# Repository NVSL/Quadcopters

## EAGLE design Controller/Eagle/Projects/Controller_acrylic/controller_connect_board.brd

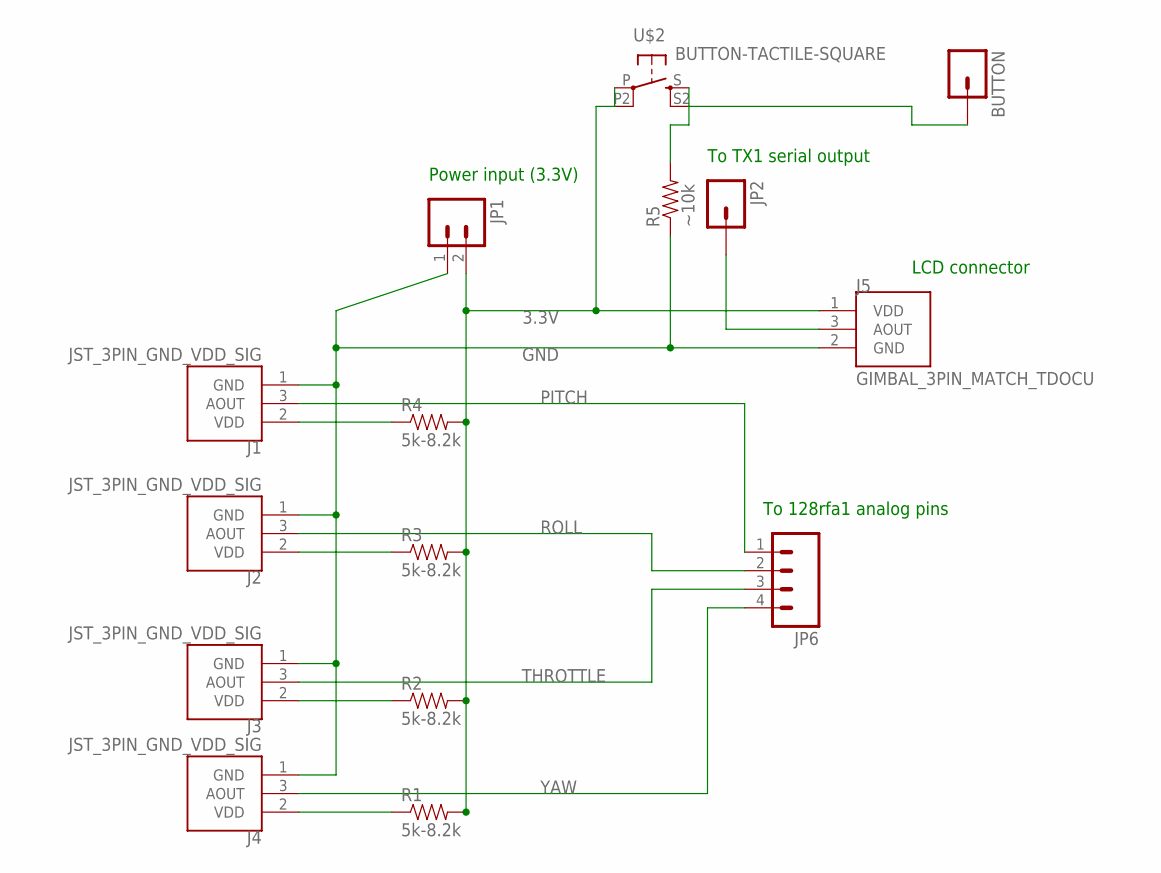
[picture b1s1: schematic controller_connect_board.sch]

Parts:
BUTTON: M01PTH; 1X01
J1, J2, J3, J4: JST_3PIN_GND_VDD_SIG; JST-3-PTH-REVERSE
J5: GIMBAL_3PIN_MATCH_TDOCU; JST-3-PTH
JP1: M021X02_NO_SILK; 1X02_NO_SILK
JP2: M01PTH; 1X01
JP6: M04PTH; 1X04
R1, R2, R3, R4: 5k-8.2k; AXIAL-0.4
R5: ~10k; AXIAL-0.4
U$2: BUTTON-TACTILE-SQUARE; BUTTON-TACTILE-SQUARE-ADAFRUIT1010

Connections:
3.3V: J5.1 (VDD), JP1.2, R1.P$2 (2), R2.P$2 (2), R3.P$2 (2), R4.P$2 (2), U$2.P, U$2.P2 (P1)
GND: J1.1 (GND), J2.1 (GND), J3.1 (GND), J4.1 (GND), J5.2 (GND), JP1.1, R5.P$1 (1)
unnamed: J4.2 (VDD), R1.P$1 (1)
unnamed: J3.2 (VDD), R2.P$1 (1)
unnamed: J2.2 (VDD), R3.P$1 (1)
unnamed: J1.2 (VDD), R4.P$1 (1)
unnamed: BUTTON.1, R5.P$2 (2), U$2.S, U$2.S2 (S1)
unnamed: J5.3 (AOUT), JP2.1
PITCH: J1.3 (AOUT), JP6.1
ROLL: J2.3 (AOUT), JP6.2
THROTTLE: J3.3 (AOUT), JP6.3
YAW: J4.3 (AOUT), JP6.4

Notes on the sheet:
Power input (3.3V)
To 128rfa1 analog pins
LCD connector
To TX1 serial output

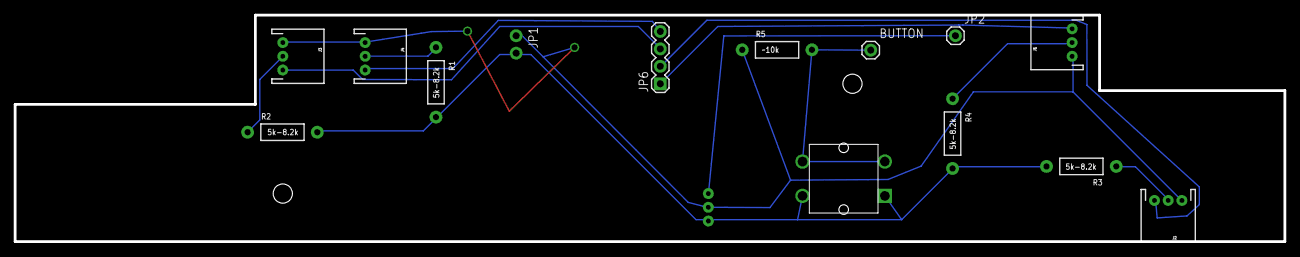
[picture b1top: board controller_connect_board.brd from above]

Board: 2 copper layers, 185.0 x 33.0 mm, 16 parts (1 on the bottom side), 12 nets.

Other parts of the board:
U$1: CONNECTOR_BOARD_OUTLINE

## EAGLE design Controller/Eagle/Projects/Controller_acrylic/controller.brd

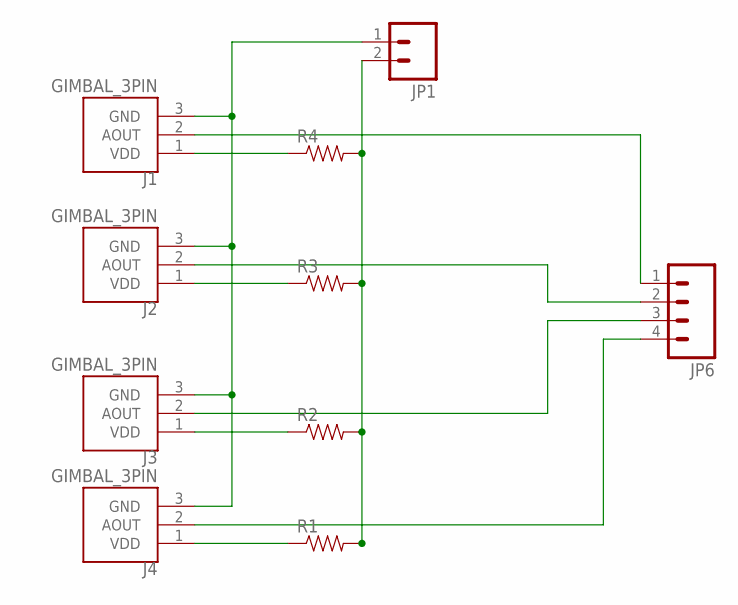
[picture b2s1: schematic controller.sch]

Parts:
J1, J2, J3, J4: GIMBAL_3PIN; JST-3-PTH
JP1: M02LOCK; 1X02_LOCK
JP6: M04PTH; 1X04
R1, R2, R3, R4: RESISTORPTH-1/6W; 1/6W-RES

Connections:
3.3V: JP1.2, R1.2, R2.2, R3.2, R4.2
GND: J1.3 (GND), J2.3 (GND), J3.3 (GND), J4.3 (GND), JP1.1
unnamed: J4.1 (VDD), R1.1
unnamed: J3.1 (VDD), R2.1
unnamed: J2.1 (VDD), R3.1
unnamed: J1.1 (VDD), R4.1
unnamed: J1.2 (AOUT), JP6.1
unnamed: J2.2 (AOUT), JP6.2
unnamed: J3.2 (AOUT), JP6.3
unnamed: J4.2 (AOUT), JP6.4

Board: 2 copper layers, 15 parts (1 on the bottom side), 10 nets, no tracks yet.

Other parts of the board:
U$1, U$2: GIMBAL_FOOTPRINT
U$3: ATMEGA128RFA1
U$4: SPARKFUN_LCD_33
U$5: CONTROLLER_OUTLINE

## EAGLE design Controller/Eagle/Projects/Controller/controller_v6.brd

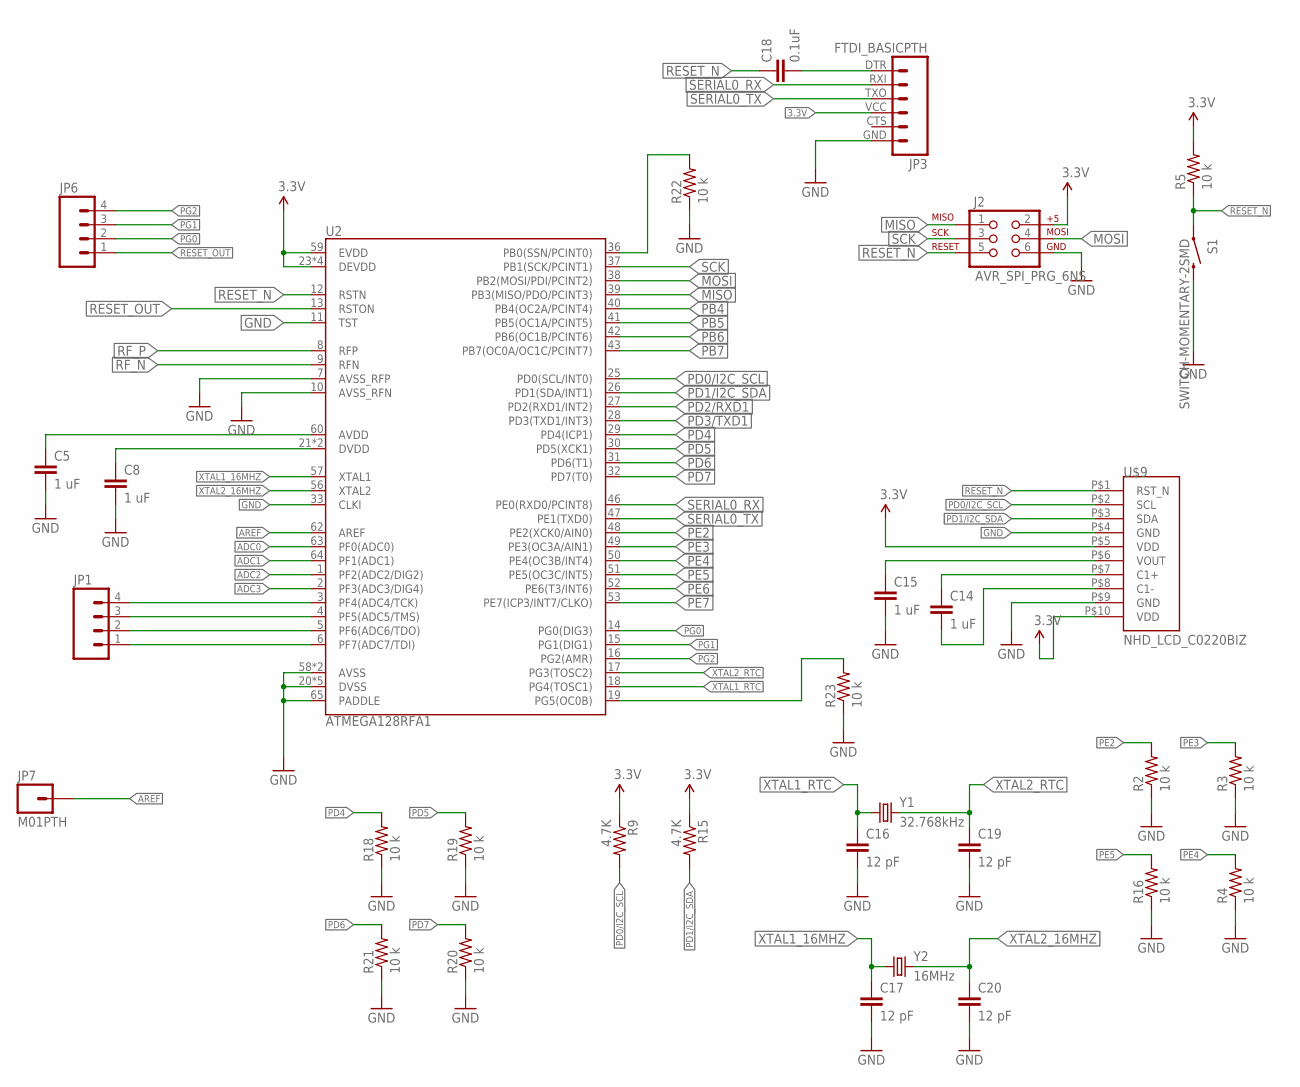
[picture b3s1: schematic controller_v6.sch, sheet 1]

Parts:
C5, C8, C14, C15: 1 uF; 0805
C16, C17, C19, C20: 12 pF; 0805
C18: 0.1uF; 0805
J2: AVR_SPI_PRG_6NS; 2X3-NS
JP1, JP6: M04PTH; 1X04
JP3: FTDI_BASICPTH; FTDI_BASIC
JP7: M01PTH; 1X01
R2, R3, R4, R5, R16, R18, R19, R20, R21, R22, R23: 10 k; 0805
R9, R15: 4.7K; 0805
S1: SWITCH-MOMENTARY-2SMD; TACTILE_SWITCH_SMD
U2: ATMEGA128RFA1; QFN-64
U$9: NHD_LCD_C0220BIZ; 1X08-2MMPTH-LCD
Y1: 32.768kHz; CRYSTAL-32KHZ-SMD
Y2: 16MHz; CRYSTAL-SMD-5X3

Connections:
3.3V: J2.2, JP3.VCC (4), R5.2, R9.1, R15.1, U2.23 (DEVDD), U2.34 (DEVDD), U2.44 (DEVDD), U2.54 (DEVDD), U2.59 (EVDD), U$9.P$5 (VDD), U$9.P$10 (VDD); also elsewhere on the board
ADC0: U2.63 (PF0(ADC0)); also elsewhere on the board
ADC1: U2.64 (PF1(ADC1)); also elsewhere on the board
ADC2: U2.1 (PF2(ADC2/DIG2)); also elsewhere on the board
ADC3: U2.2 (PF3(ADC3/DIG4)); also elsewhere on the board
ADC4: JP1.4, U2.3 (PF4(ADC4/TCK))
ADC5: JP1.3, U2.4 (PF5(ADC5/TMS))
ADC6: JP1.2, U2.5 (PF6(ADC6/TDO))
ADC7: JP1.1, U2.6 (PF7(ADC7/TDI))
AREF: JP7.1, U2.62 (AREF)
GND: C5.2, C8.2, C15.2, C16.2, C17.2, C19.2, C20.2, J2.6, JP3.GND (6), R2.1, R3.1, R4.1, R16.1, R18.1, R19.1, R20.1, R21.1, R22.1, R23.1, S1.3 (2), U2.7 (AVSS_RFP), U2.10 (AVSS_RFN), U2.11 (TST), U2.20 (DVSS), U2.24 (DVSS), U2.33 (CLKI), U2.35 (DVSS), U2.45 (DVSS), U2.55 (DVSS), U2.58 (AVSS), U2.61 (AVSS), U2.65 (PADDLE), U$9.P$4 (GND), U$9.P$9 (GND); also elsewhere on the board
MISO: J2.1, U2.39 (PB3(MISO/PDO/PCINT3))
MOSI: J2.4, U2.38 (PB2(MOSI/PDI/PCINT2))
unnamed: C18.2, JP3.DTR (1)
unnamed: C14.1, U$9.P$7 (C1+)
unnamed: C5.1, U2.60 (AVDD)
unnamed: C8.1, U2.21 (DVDD), U2.22 (DVDD)
unnamed: C14.2, U$9.P$8 (C1-)
PB0: R22.2, U2.36 (PB0(SSN/PCINT0))
PB1: R23.2, U2.19 (PG5(OC0B))
PB4: U2.40 (PB4(OC2A/PCINT4)); also elsewhere on the board
PB5: U2.41 (PB5(OC1A/PCINT5)); also elsewhere on the board
PB6: U2.42 (PB6(OC1B/PCINT6)); also elsewhere on the board
PB7: U2.43 (PB7(OC0A/OC1C/PCINT7)); also elsewhere on the board
PD0/I2C_SCL: R9.2, U2.25 (PD0(SCL/INT0)), U$9.P$2 (SCL)
PD1/I2C_SDA: R15.2, U2.26 (PD1(SDA/INT1)), U$9.P$3 (SDA)
PD2/RXD1: U2.27 (PD2(RXD1/INT2)); also elsewhere on the board
PD3/TXD1: U2.28 (PD3(TXD1/INT3)); also elsewhere on the board
PD4: R18.2, U2.29 (PD4(ICP1))
PD5: R19.2, U2.30 (PD5(XCK1))
PD6: R21.2, U2.31 (PD6(T1))
PD7: R20.2, U2.32 (PD7(T0))
PE2: R2.2, U2.48 (PE2(XCK0/AIN0))
PE3: R3.2, U2.49 (PE3(OC3A/AIN1))
PE4: R4.2, U2.50 (PE4(OC3B/INT4))
PE5: R16.2, U2.51 (PE5(OC3C/INT5))
PE6: U2.52 (PE6(T3/INT6)); also elsewhere on the board
PE7: U2.53 (PE7(ICP3/INT7/CLKO)); also elsewhere on the board
PG0: JP6.2, U2.14 (PG0(DIG3))
PG1: JP6.3, U2.15 (PG1(DIG1))
PG2: JP6.4, U2.16 (PG2(AMR))
RESET_N: C18.1, J2.5, R5.1, S1.1, U2.12 (RSTN), U$9.P$1 (RST_N)
RESET_OUT: JP6.1, U2.13 (RSTON)
RF_N: U2.9 (RFN); also elsewhere on the board
RF_P: U2.8 (RFP); also elsewhere on the board
SCK: J2.3, U2.37 (PB1(SCK/PCINT1))
SERIAL0_RX: JP3.RXI (2), U2.46 (PE0(RXD0/PCINT8))
SERIAL0_TX: JP3.TXO (3), U2.47 (PE1(TXD0))
VOUT: C15.1, U$9.P$6 (VOUT)
XTAL1_16MHZ: C17.1, U2.57 (XTAL1), Y2.1
XTAL1_RTC: C16.1, U2.18 (PG4(TOSC1)), Y1.X1 (1)
XTAL2_16MHZ: C20.1, U2.56 (XTAL2), Y2.3 (2)
XTAL2_RTC: C19.1, U2.17 (PG3(TOSC2)), Y1.X2 (2)

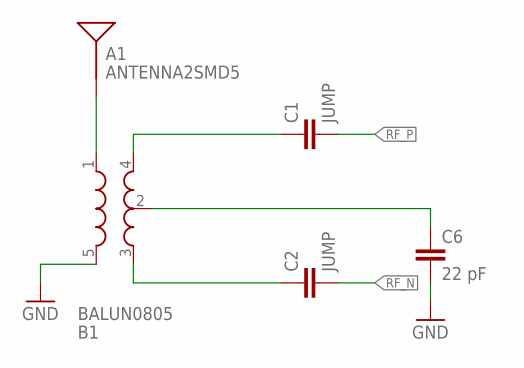
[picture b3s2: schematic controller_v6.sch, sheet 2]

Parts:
A1: ANTENNA2SMD5; ANTENNA-CHIP5
B1: BALUN0805; BALUN
C1, C2: JUMP; 0805
C6: 22 pF; 0805

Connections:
GND: B1.5 (GND), C6.2; also elsewhere on the board
unnamed: B1.4 (OUT1), C1.1
unnamed: B1.3 (OUT2), C2.1
unnamed: B1.2 (GND), C6.1
unnamed: A1.FEED, B1.1 (IN)
RF_N: C2.2; also elsewhere on the board
RF_P: C1.2; also elsewhere on the board

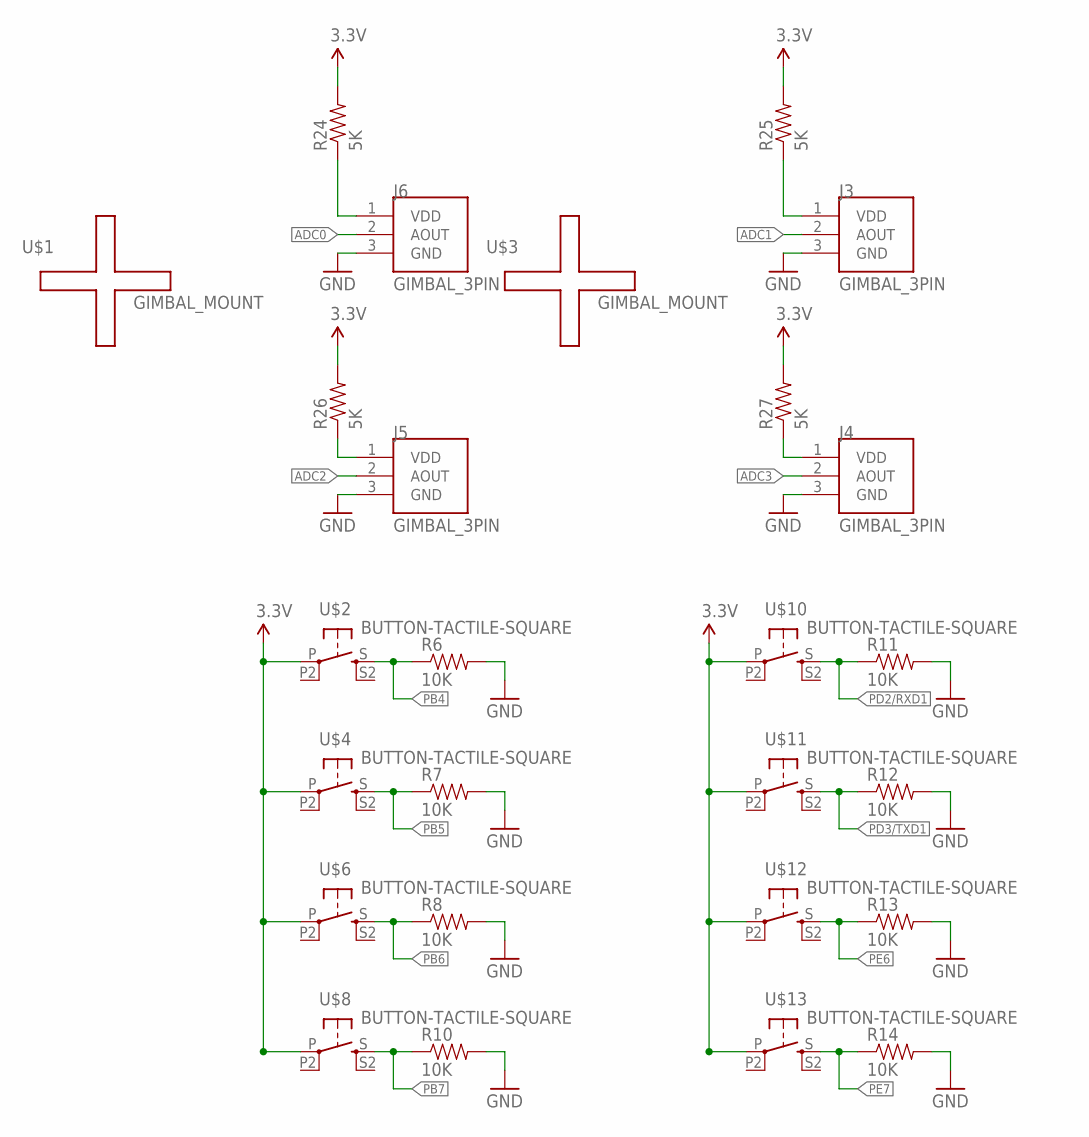
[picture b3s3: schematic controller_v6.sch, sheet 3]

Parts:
J3, J4, J5, J6: GIMBAL_3PIN; JST-3-PTH
R6, R7, R8, R10, R11, R12, R13, R14: 10K; 0805
R24, R25, R26, R27: 5K; 0805
U$1, U$3: GIMBAL_MOUNT; GIMBAL_FOOTPRINT
U$2, U$4, U$6, U$8, U$10, U$11, U$12, U$13: BUTTON-TACTILE-SQUARE; BUTTON-TACTILE-SQUARE-ADAFRUIT1010

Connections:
3.3V: R24.2, R25.2, R26.2, R27.2, U$2.P, U$4.P, U$6.P, U$8.P, U$10.P, U$11.P, U$12.P, U$13.P; also elsewhere on the board
ADC0: J6.2 (AOUT); also elsewhere on the board
ADC1: J3.2 (AOUT); also elsewhere on the board
ADC2: J5.2 (AOUT); also elsewhere on the board
ADC3: J4.2 (AOUT); also elsewhere on the board
GND: J3.3 (GND), J4.3 (GND), J5.3 (GND), J6.3 (GND), R6.2, R7.2, R8.2, R10.2, R11.2, R12.2, R13.2, R14.2; also elsewhere on the board
unnamed: J6.1 (VDD), R24.1
unnamed: J3.1 (VDD), R25.1
unnamed: J5.1 (VDD), R26.1
unnamed: J4.1 (VDD), R27.1
PB4: R6.1, U$2.S; also elsewhere on the board
PB5: R7.1, U$4.S; also elsewhere on the board
PB6: R8.1, U$6.S; also elsewhere on the board
PB7: R10.1, U$8.S; also elsewhere on the board
PD2/RXD1: R11.1, U$10.S; also elsewhere on the board
PD3/TXD1: R12.1, U$11.S; also elsewhere on the board
PE6: R13.1, U$12.S; also elsewhere on the board
PE7: R14.1, U$13.S; also elsewhere on the board

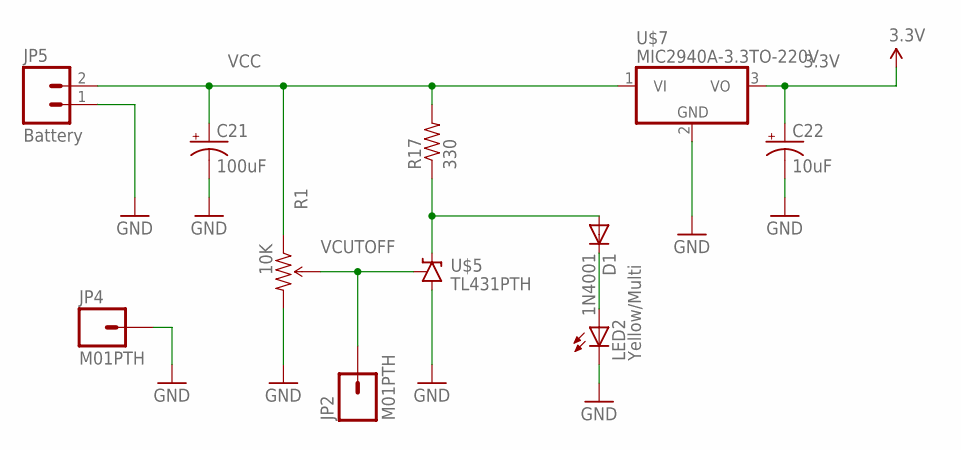
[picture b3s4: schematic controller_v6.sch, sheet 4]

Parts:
C21: 100uF; E3,5-8
C22: 10uF; E2,5-5
D1: 1N4001; DO41-10
JP2, JP4: M01PTH; 1X01
JP5: Battery; 1X02
LED2: Yellow/Multi; LED5MM
R1: 10K; 3386U
R17: 330; AXIAL-0.3
U$5: TL431PTH; TO-92
U$7: MIC2940A-3.3TO-220V; TO-220V

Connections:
3.3V: C22.+, U$7.3 (VO); also elsewhere on the board
GND: C21.-, C22.-, JP4.1, JP5.1, LED2.K (C), R1.3 (CW), U$5.2 (A), U$7.2 (GND); also elsewhere on the board
unnamed: D1.A, R17.P$1 (1), U$5.3 (C)
unnamed: D1.C, LED2.A
VCC: C21.+, JP5.2, R1.1 (CCW), R17.P$2 (2), U$7.1 (VI)
VCUTOFF: JP2.1, R1.2 (WIPER), U$5.1 (R)

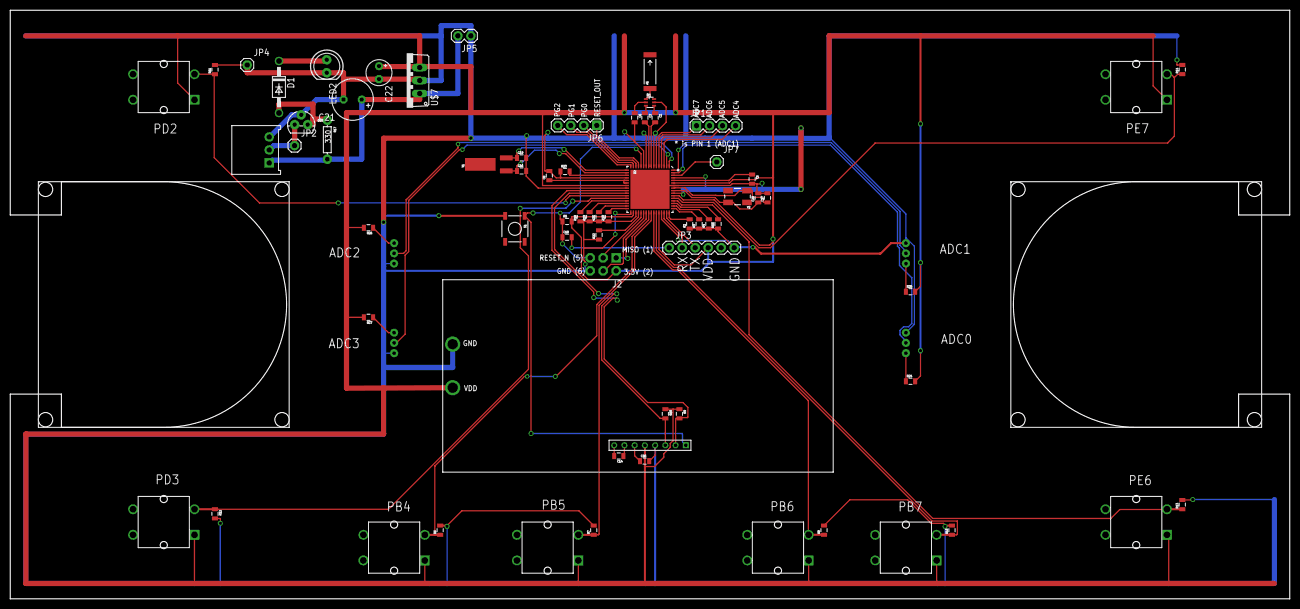
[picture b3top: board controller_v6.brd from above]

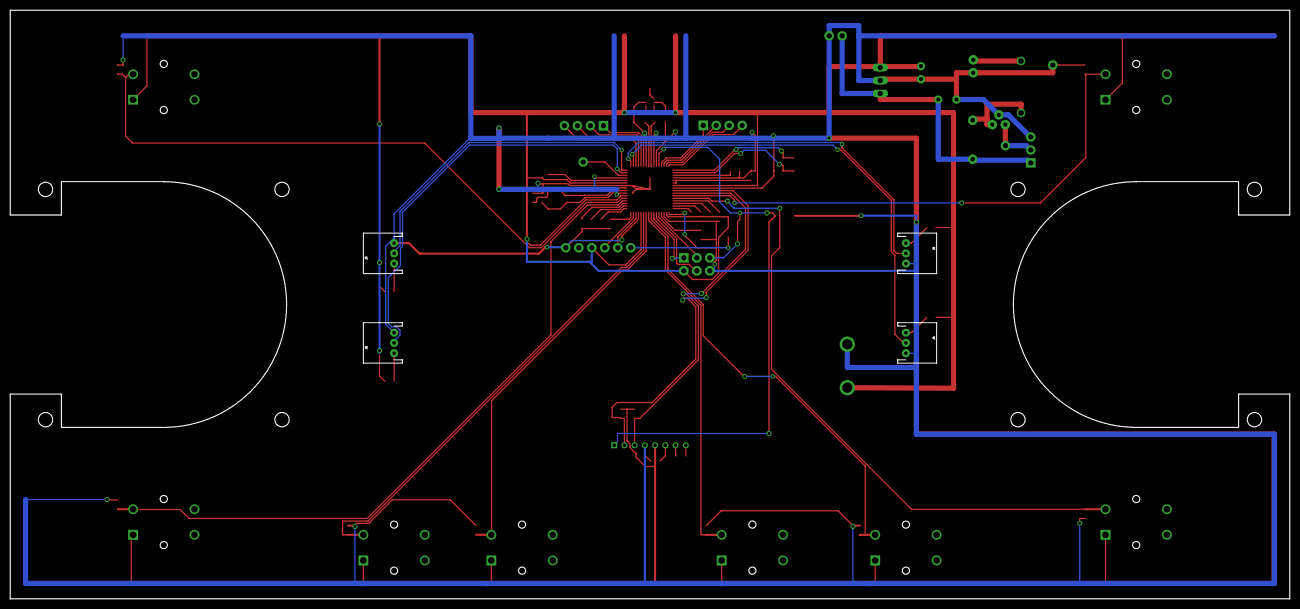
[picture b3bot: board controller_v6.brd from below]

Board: 2 copper layers, 250.0 x 115.0 mm, 74 parts (4 on the bottom side), 65 nets.

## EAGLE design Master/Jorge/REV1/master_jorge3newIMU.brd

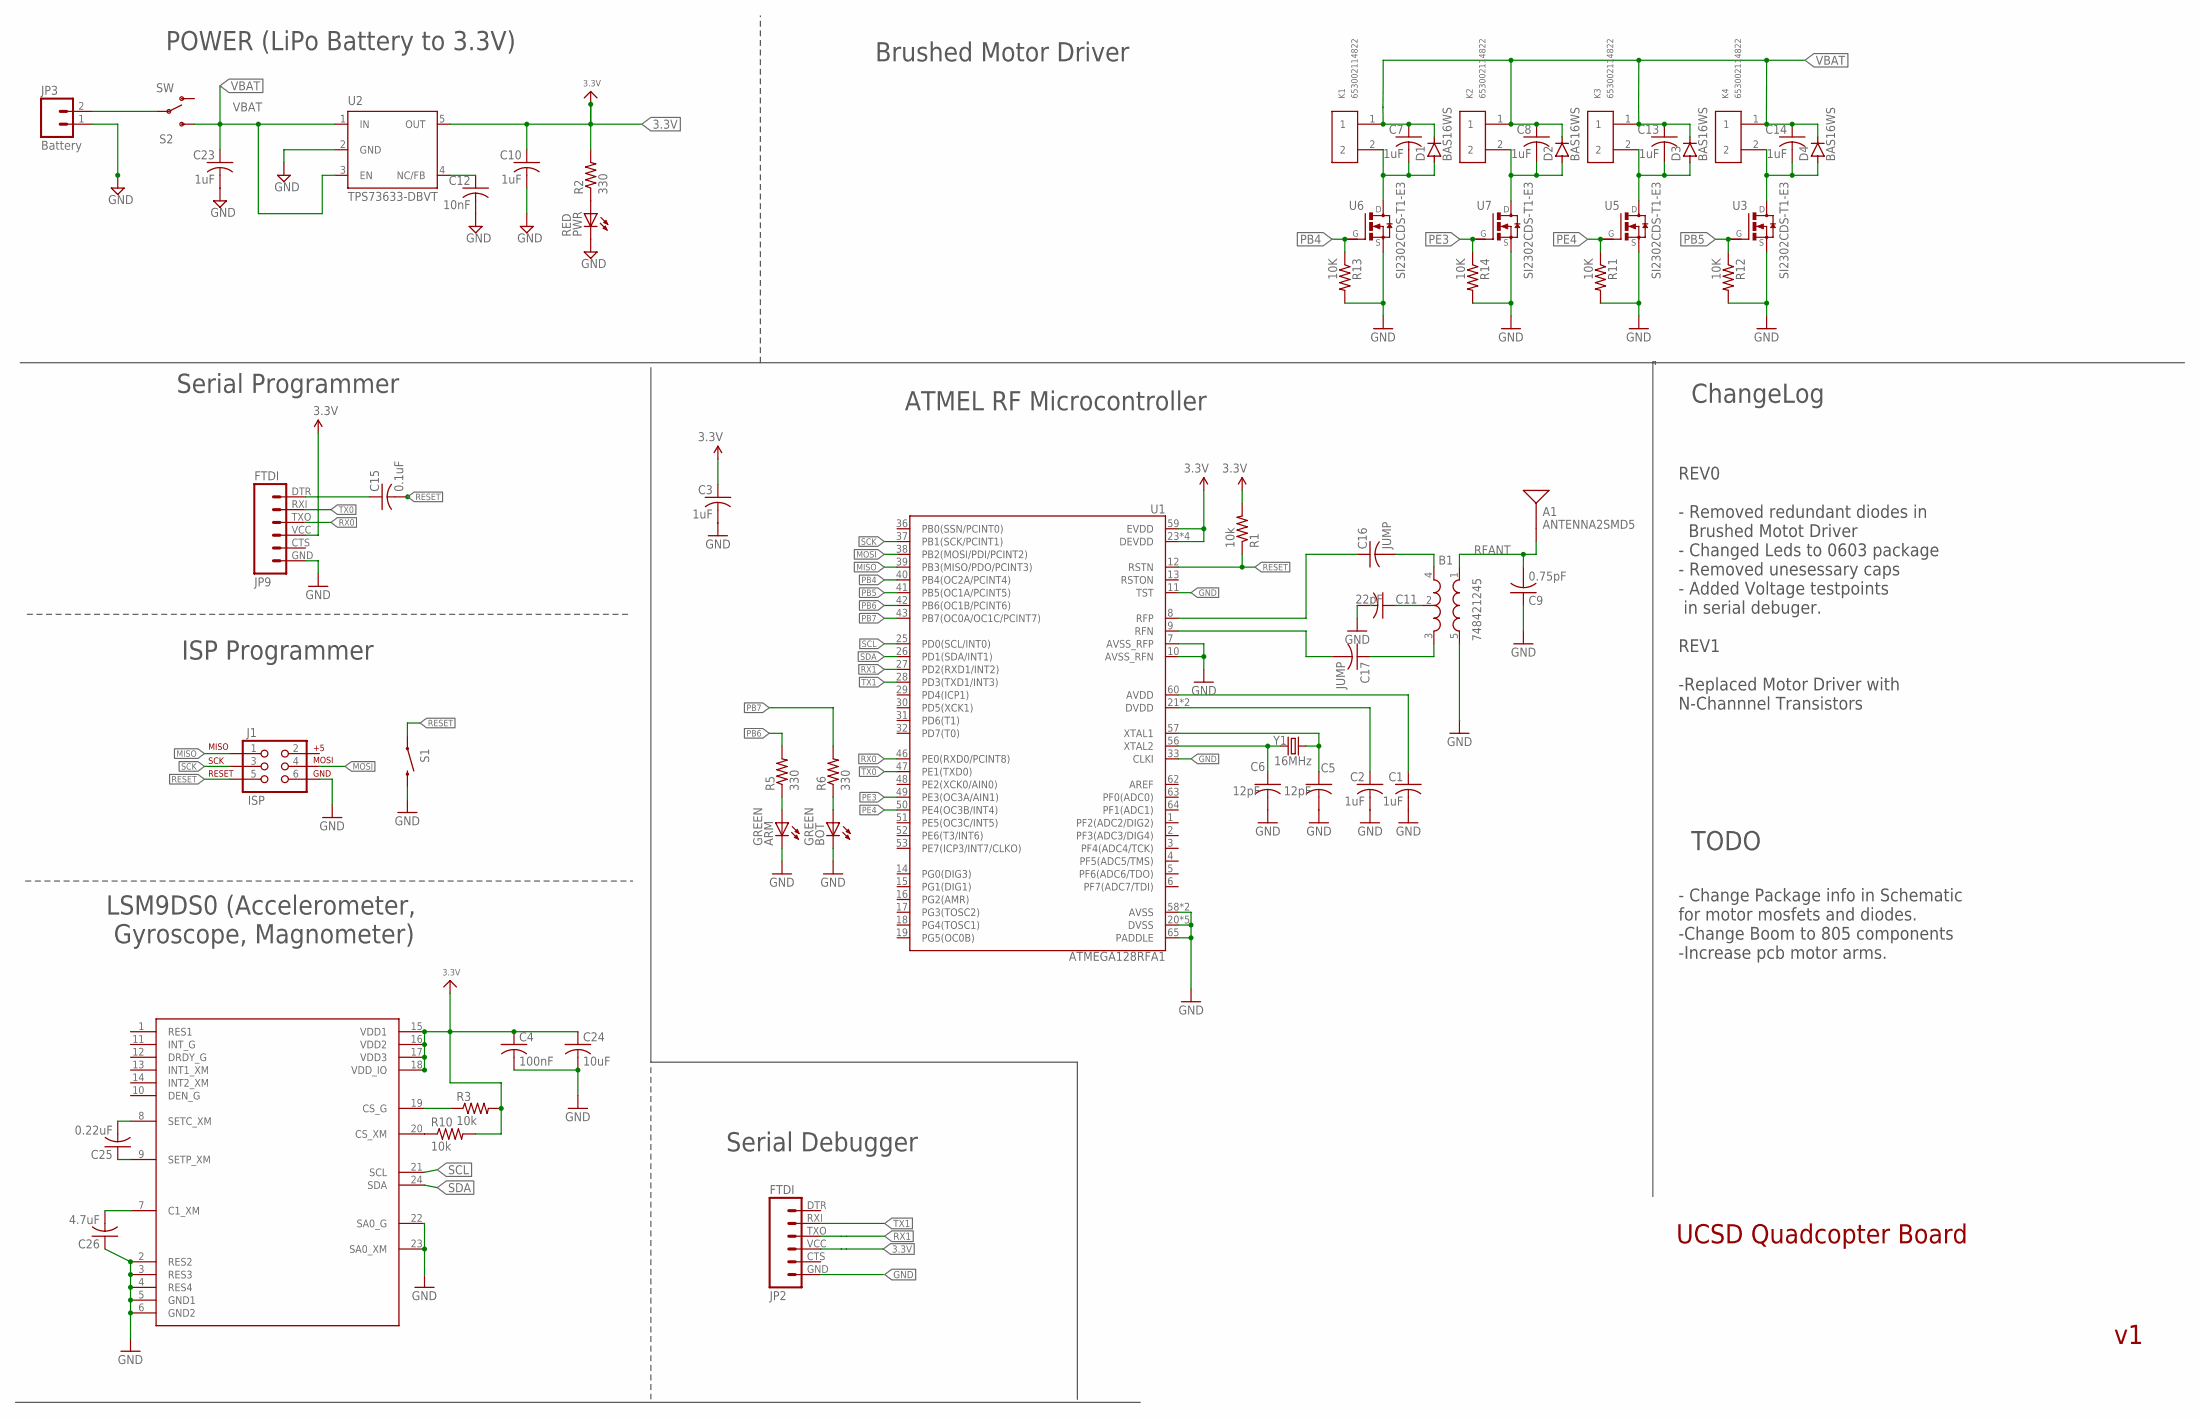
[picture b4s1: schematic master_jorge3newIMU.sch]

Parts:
A1: ANTENNA2SMD5; ANTENNA-CHIP5
ARM: GREEN; CHIP-LED0805
B1: 748421245; BALUN
BOT: GREEN; CHIP-LED0805
C1, C2, C3, C7, C8, C10, C13, C14, C23: 1uF; C0805
C4: 100nF; C0805
C5, C6: 12pF; C0805
C9: 0.75pF; C0805
C11: 22pF; C0805
C12: 10nF; C0805
C15: 0.1uF; C0805
C16, C17: JUMP; C0805
C24: 10uF; C0805
C25: 0.22uF; C0805
C26: 4.7uF; C0805
D1, D2, D3, D4: BAS16WS; SOD323_ST
J1: ISP; 2X3-NS
JP2, JP9: FTDI; FTDI_BASIC
JP3: Battery; 1X02
K1, K2, K3, K4: 653002114822
PWR: RED; CHIP-LED0805
R1, R3, R10: 10k; R0805
R2, R5, R6: 330; R0805
R11, R12, R13, R14: 10K; R0805
S1: SWITCH-MOMENTARY-2SMD; TACTILE_SWITCH_SMD
S2: SW; SWITCH-SPDT
U1: ATMEGA128RFA1; QFN-64
U2: TPS73633-DBVT; SOT23-DBV
U3, U5, U6, U7: SI2302CDS-T1-E3; SOT95P237X112-3N
U4: LSM9DS0; LGA-24
Y1: 16MHz; CRYSTAL-SMD-5X3

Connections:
3.3V: C3.1, C4.1, C10.1, C24.1, JP2.VCC (4), JP9.VCC (4), R1.2, R2.2, R3.2, R10.2, U1.23 (DEVDD), U1.34 (DEVDD), U1.44 (DEVDD), U1.54 (DEVDD), U1.59 (EVDD), U2.5 (OUT), U4.15 (VDD1), U4.16 (VDD2), U4.17 (VDD3), U4.18 (VDD_IO)
AVDD: C1.1, U1.60 (AVDD)
DTR: C15.1, JP9.DTR (1)
DVDD: C2.1, U1.21 (DVDD), U1.22 (DVDD)
GND: ARM.C, B1.5 (GND), BOT.C, C1.2, C2.2, C3.2, C4.2, C5.2, C6.2, C9.1, C10.2, C11.2, C12.2, C23.2, C24.2, C26.1, J1.6, JP2.GND (6), JP3.1, JP9.GND (6), PWR.C, R11.2, R12.2, R13.2, R14.2, S1.3 (2), U1.7 (AVSS_RFP), U1.10 (AVSS_RFN), U1.11 (TST), U1.20 (DVSS), U1.24 (DVSS), U1.33 (CLKI), U1.35 (DVSS), U1.45 (DVSS), U1.55 (DVSS), U1.58 (AVSS), U1.61 (AVSS), U1.65 (PADDLE), U2.2 (GND), U3.2 (S), U4.2 (RES2), U4.3 (RES3), U4.4 (RES4), U4.5 (GND1), U4.6 (GND2), U4.22 (SA0_G), U4.23 (SA0_XM), U5.2 (S), U6.2 (S), U7.2 (S)
MISO: J1.1, U1.39 (PB3(MISO/PDO/PCINT3))
MOSI: J1.4, U1.38 (PB2(MOSI/PDI/PCINT2))
unnamed: C12.1, U2.4 (NC/FB)
unnamed: PWR.A, R2.1
unnamed: C5.1, U1.57 (XTAL1), Y1.3 (2)
unnamed: C6.1, U1.56 (XTAL2), Y1.1
unnamed: B1.2 (GND), C11.1
unnamed: ARM.A, R5.1
unnamed: B1.4 (OUT1), C16.2
unnamed: B1.3 (OUT2), C17.1
unnamed: BOT.A, R6.1
unnamed: JP3.2, S2.2
unnamed: C26.2, U4.7 (C1_XM)
unnamed: C25.2, U4.8 (SETC_XM)
unnamed: C25.1, U4.9 (SETP_XM)
unnamed: R3.1, U4.19 (CS_G)
unnamed: R10.1, U4.20 (CS_XM)
unnamed: C7.2, D1.A, K1.2, U6.3 (D)
unnamed: C8.2, D2.A, K2.2, U7.3 (D)
unnamed: C13.2, D3.A, K3.2, U5.3 (D)
unnamed: C14.2, D4.A, K4.2, U3.3 (D)
PB4: R13.1, U1.40 (PB4(OC2A/PCINT4)), U6.1 (G)
PB5: R12.1, U1.41 (PB5(OC1A/PCINT5)), U3.1 (G)
PB6: R5.2, U1.42 (PB6(OC1B/PCINT6))
PB7: R6.2, U1.43 (PB7(OC0A/OC1C/PCINT7))
PE3: R14.1, U1.49 (PE3(OC3A/AIN1)), U7.1 (G)
PE4: R11.1, U1.50 (PE4(OC3B/INT4)), U5.1 (G)
RESET: C15.2, J1.5, R1.1, S1.1, U1.12 (RSTN)
RFANT: A1.FEED, B1.1 (IN), C9.2
RFN: C17.2, U1.9 (RFN)
RFP: C16.1, U1.8 (RFP)
RX0: JP9.TXO (3), U1.46 (PE0(RXD0/PCINT8))
RX1: JP2.TXO (3), U1.27 (PD2(RXD1/INT2))
SCK: J1.3, U1.37 (PB1(SCK/PCINT1))
SCL: U1.25 (PD0(SCL/INT0)), U4.21 (SCL)
SDA: U1.26 (PD1(SDA/INT1)), U4.24 (SDA)
TX0: JP9.RXI (2), U1.47 (PE1(TXD0))
TX1: JP2.RXI (2), U1.28 (PD3(TXD1/INT3))
VBAT: C7.1, C8.1, C13.1, C14.1, C23.1, D1.C, D2.C, D3.C, D4.C, K1.1, K2.1, K3.1, K4.1, S2.3 (S), U2.1 (IN), U2.3 (EN)

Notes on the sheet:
LSM9DS0 (Accelerometer, Gyroscope, Magnometer)
POWER (LiPo Battery to 3.3V)
Brushed Motor Driver
UCSD Quadcopter Board
Serial Programmer
ISP Programmer
Serial Debugger
ATMEL RF Microcontroller
ChangeLog
REV0 - Removed redundant diodes in Brushed Motot Driver - Changed Leds to 0603 package - Removed unesessary caps - Added Voltage testpoints in serial debuger. REV1 -Replaced Motor Driver with N-Channnel Transistors
TODO
- Change Package info in Schematic for motor mosfets and diodes. -Change Boom to 805 components -Increase pcb motor arms.

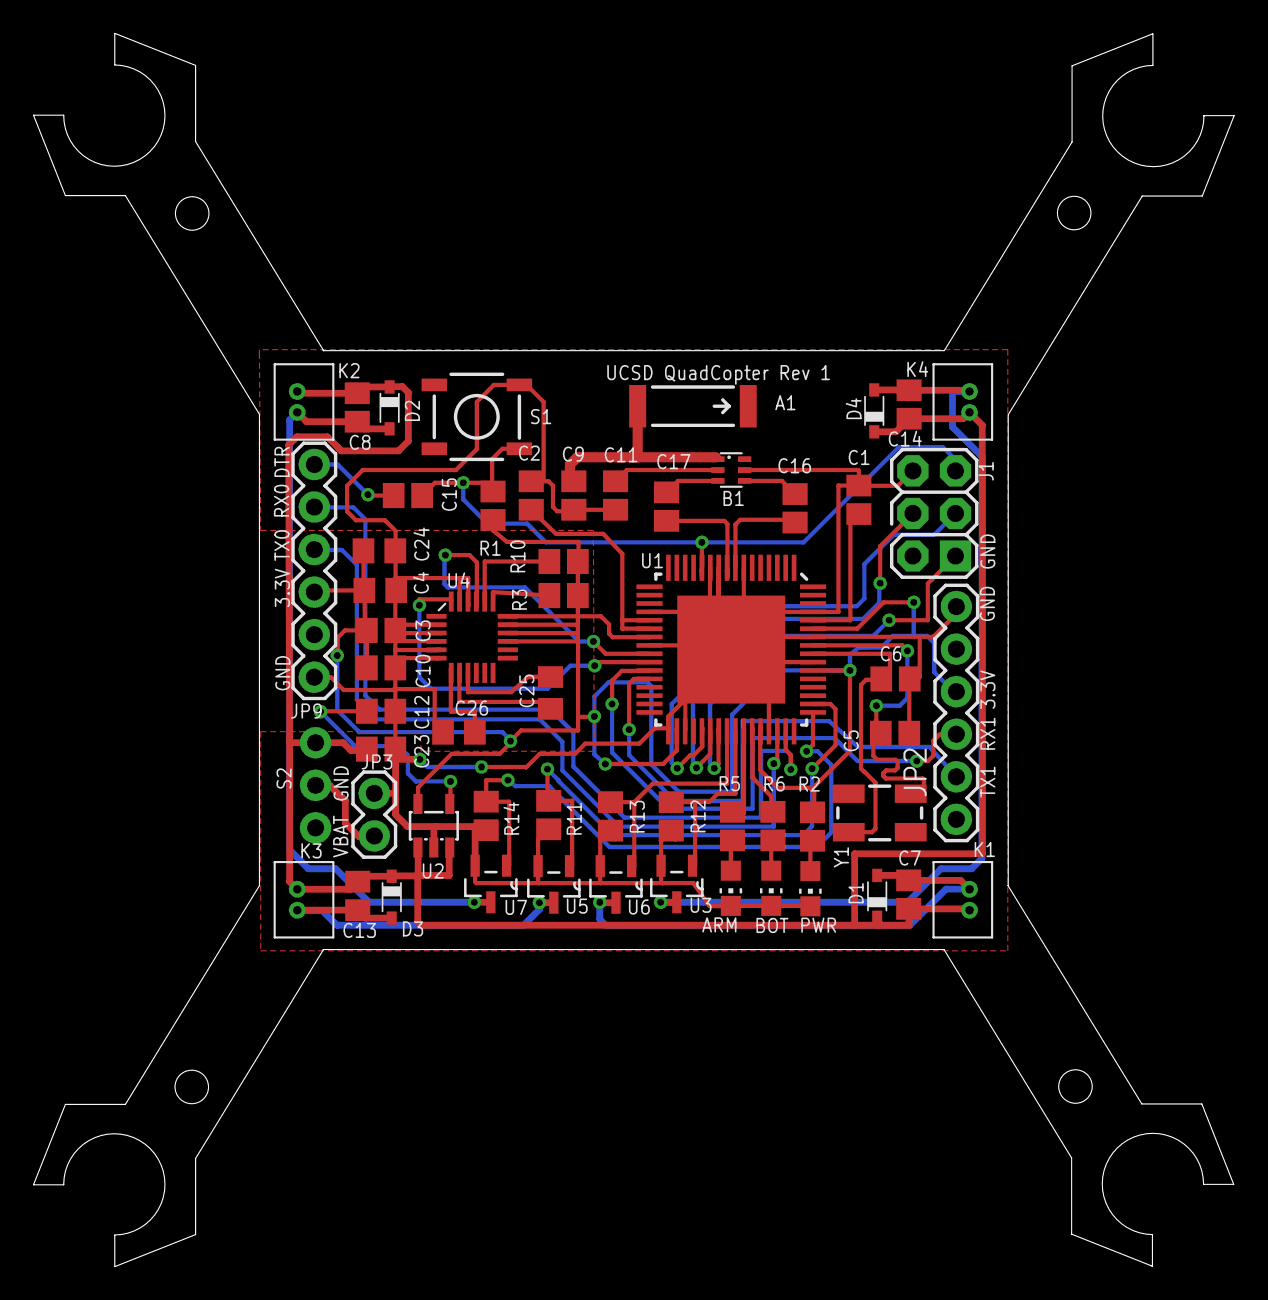
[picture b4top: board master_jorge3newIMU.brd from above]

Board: 2 copper layers, 71.7 x 73.6 mm, 58 parts (0 on the bottom side), 44 nets.

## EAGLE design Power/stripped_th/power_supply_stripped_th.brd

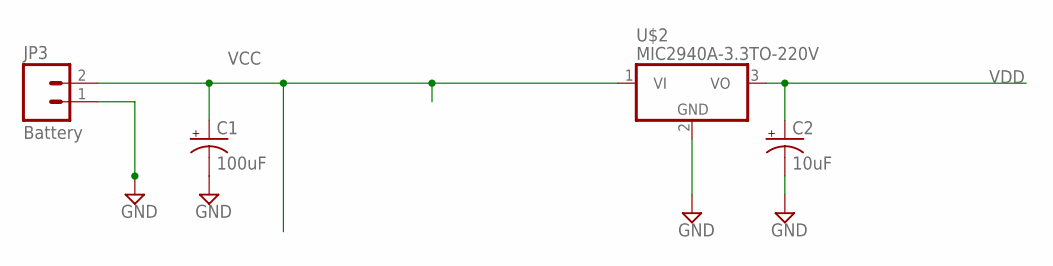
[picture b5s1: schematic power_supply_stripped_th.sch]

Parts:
C1: 100uF; E3,5-8
C2: 10uF; E2,5-5
JP3: Battery; 1X02
U$2: MIC2940A-3.3TO-220V; TO-220V

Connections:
GND: C1.-, C2.-, JP3.1, U$2.2 (GND)
VCC: C1.+, JP3.2, U$2.1 (VI)
VDD: C2.+, U$2.3 (VO)

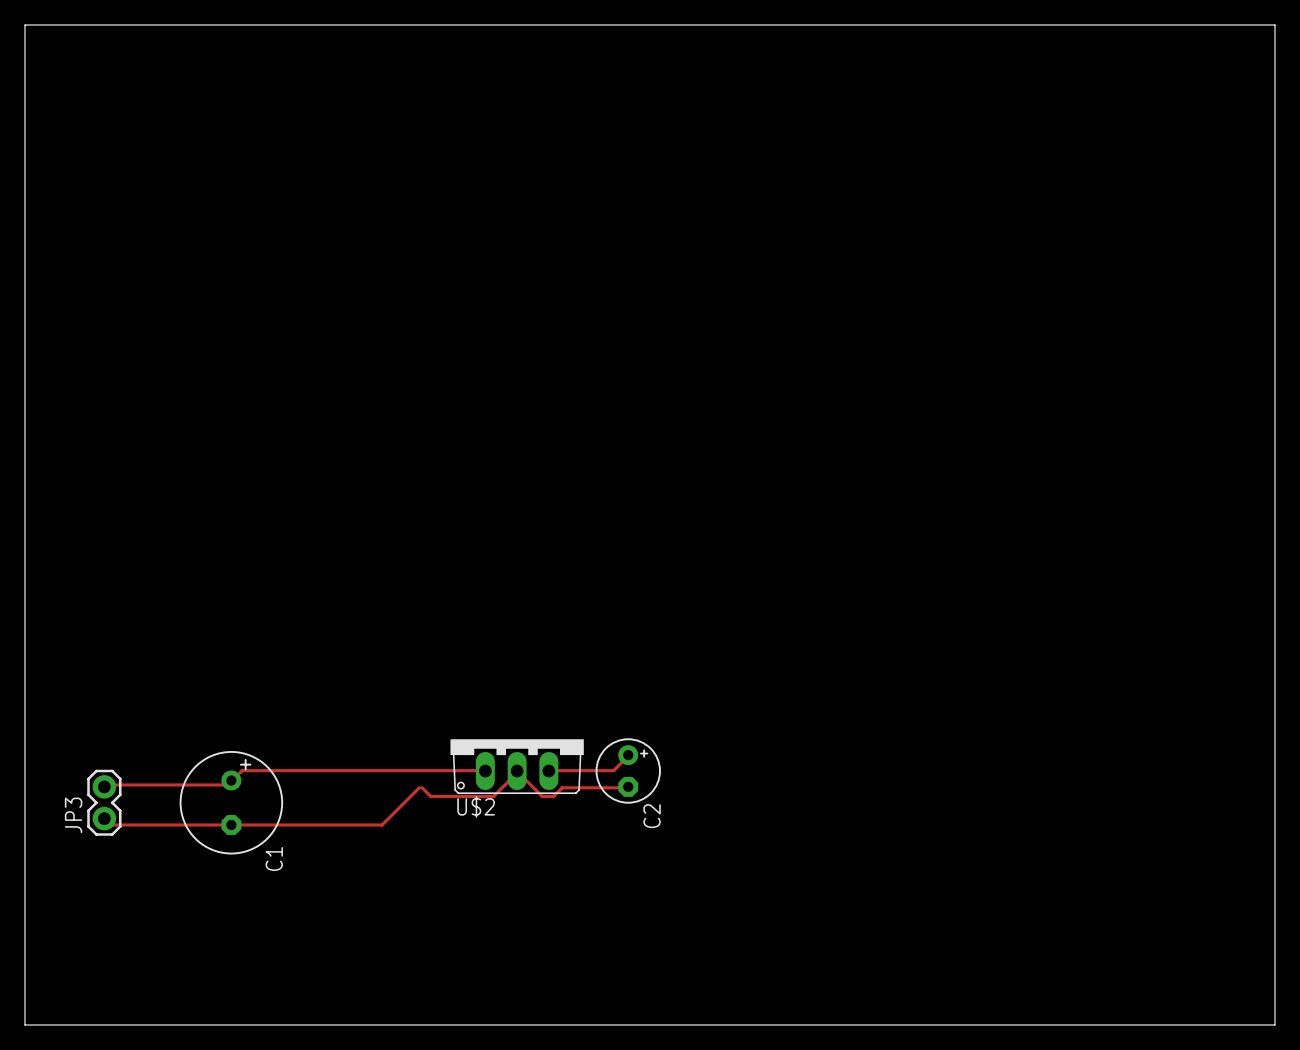
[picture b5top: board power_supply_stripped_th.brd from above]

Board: 2 copper layers, 100.0 x 80.0 mm, 4 parts (0 on the bottom side), 3 nets.

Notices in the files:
parts and their libraries:
SparkFun-Resistors: Licensing: Creative Commons ShareAlike 4.0 International - https://creativecommons.org/licenses/by-sa/4.0
SparkFun-Aesthetics: Licensing: CC v3.0 Share-Alike You are welcome to use this library for commercial purposes.
